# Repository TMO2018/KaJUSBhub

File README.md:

# KaJUSBhub
USB-Adapter zum Einbau in ein C64-Gehäuse für die C64-Tastatur und -Joysticks zum Anschluss an den MiSTer

Auf der Platine enthalten sind:

- ein USB-Adapter dür die C64-Tastatur und -9-pol. Joystcks
- der USB-Hub des MiSTers
- eine über Feinsicherungen abgesicherte Stromversorgung für den MiSter, USB-Adapter und USB-Hub

Die Spannungsversorgung erfolgt mit einem C64-Netzteil.

Rev 0.1:
Version mit einem gemeinsamen Mikrocontroller PIC18F4550 für C64-Tastatur und -Joysticks

Rev 0.2:
Version mit seperaten Mikrocontrollern PIC18F4550 für C64-Tastatur und -Joysticks

Die Firmware basiert auf dem Projekt C64 VICE front-end von Simon Inns.
https://www.waitingforfriday.com/?p=470

Rev 0.1

Hinweis: In den Schaltplänen der Versionen 0.1 und 0.2 ist der Mikrokontroller mit PIC18F4450 beschriftet. Richtig ist aber PIC18F4550. Beide Mikrokontroller sind pin-kompatibel.

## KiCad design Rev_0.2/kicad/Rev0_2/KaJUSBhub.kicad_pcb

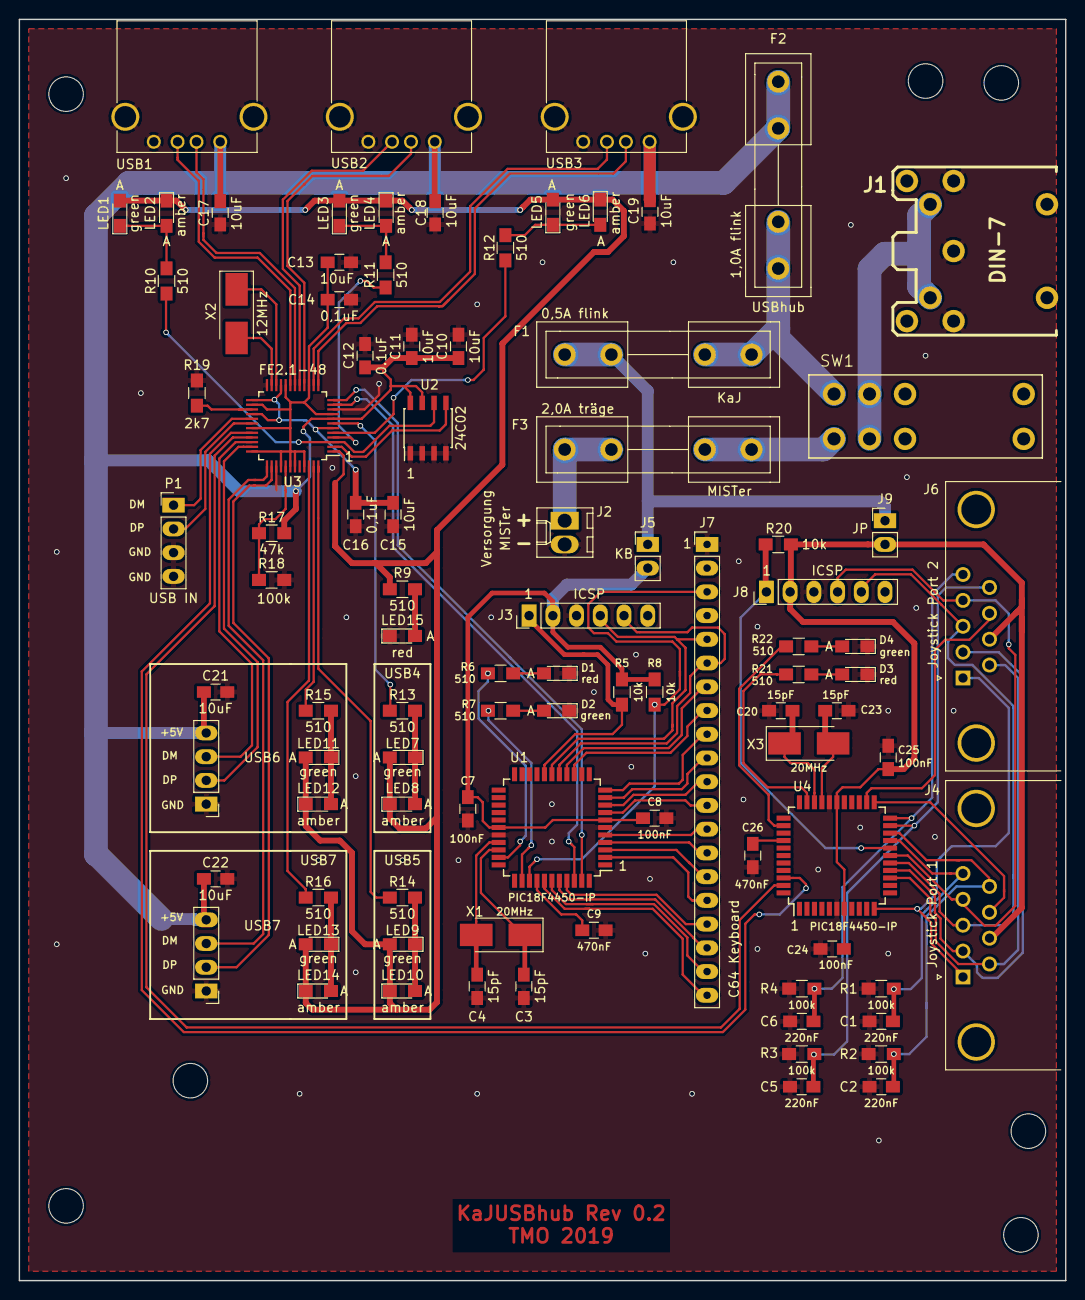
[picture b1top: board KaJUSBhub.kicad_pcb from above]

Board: 2 copper layers, 112.0 x 135.0 mm, 98 parts (0 on the bottom side), 92 nets.

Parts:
C1, C2, C5, C6: 220nF; C_0805_HandSoldering
C3, C4, C20, C23: 15pF; C_0805_HandSoldering
C7, C8, C24, C25: 100nF; C_0805_HandSoldering
C9, C26: 470nF; C_0805_HandSoldering
C10, C11, C13, C15, C17, C18, C19, C21, C22: 10uF; C_0805_HandSoldering
C12: 0.1uF; C_0805_HandSoldering
C14, C16: 0,1uF; C_0805_HandSoldering
D1, D3: red; LED_0805_HandSoldering
D2, D4: green; LED_0805_HandSoldering
F1: 0,5A flink; Fuseholder5x20_horiz_open_inline_Type-I
F2: 1,0A flink; Fuseholder5x20_horiz_open_inline_Type-I
F3: 2,0A träge; Fuseholder5x20_horiz_open_inline_Type-I
J1: DIN-7; din-7
J2: Versorgung MISTer; Molex_KK-6410-02_02x2.54mm_Straight
J3, J8: ICSP; Pin_Header_Straight_1x06_Pitch2.54mm
J4: Joystick Port 1; DSUB-9_Male_Horizontal_Pitch2.77x2.84mm_EdgePinOffset7.70mm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
J5: KB; Pin_Header_Straight_1x02_Pitch2.54mm
J6: Joystick Port 2; DSUB-9_Male_Horizontal_Pitch2.77x2.84mm_EdgePinOffset7.70mm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
J7: C64 Keyboard; Pin_Header_Straight_1x20_Pitch2.54mm_long_pad
J9: JP; Pin_Header_Straight_1x02_Pitch2.54mm
LED1, LED3, LED5, LED7, LED9, LED11, LED13: green; LED_0805_HandSoldering
LED2, LED4, LED6, LED8, LED10, LED12, LED14: amber; LED_0805_HandSoldering
LED15: red; LED_0805_HandSoldering
MH1, MH2, MH3, MH4, MH5: Conn_01x01; MountingHole_3.7mm
P1: USB IN; Pin_Header_Straight_1x04_Pitch2.54mm_long_pad
R1, R2, R3, R4, R18: 100k; R_0805_HandSoldering
R5, R8, R20: 10k; R_0805_HandSoldering
R6, R7, R9, R10, R11, R12, R13, R14, R15, R16, R21, R22: 510; R_0805_HandSoldering
R17: 47k; R_0805_HandSoldering
R19: 2k7; R_0805_HandSoldering
SW1: DPDT_SWITCH
U1, U4: PIC18F4450-IP; TQFP-44_10x10mm_Pitch0.8mm
U2: 24C02; SOIC-8_3.9x4.9mm_Pitch1.27mm
U3: FE2.1-48; LQFP-48_7x7mm_Pitch0.5mm
USB1, USB2, USB3: USB_A
USB6: USB out; Pin_Header_Straight_1x04_Pitch2.54mm_long_pad
USB7: USB out; Pin_Header_Straight_1x04_Pitch2.54mm
X1, X3: 20MHz; Crystal_SMD_5032-2pin_5.0x3.2mm_HandSoldering
X2: 12MHz; Crystal_SMD_5032-2pin_5.0x3.2mm_HandSoldering

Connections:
+5VJP: C24.2, C25.1, J4.7, J6.7, J8.2, J9.2, R20.1, U4.7, U4.28
+5VKB: C7.2, C8.2, J3.2, J5.2, R5.1, R8.1, U1.7, U1.28
+5VKaJ: F1.1, J5.1, J9.1
+5VUSBhub: C10.1, C11.1, C12.1, C17.1, C18.1, C19.1, C21.1, C22.1, F2.1, R17.2, U2.7, U2.8, U3.8, USB1.1, USB2.1, USB3.1, USB6.4, USB7.4
DM1: U3.18, USB1.2
DM2: U3.16, USB2.2
DM3: U3.13, USB3.2
DM4: U1.42, U3.11
DM5: U3.32, U4.42
DM6: U3.34, USB6.3
DM7: U3.37, USB7.3
DMU: P1.1, U3.29
DP1: U3.19, USB1.3
DP2: U3.17, USB2.3
DP3: U3.14, USB3.3
DP4: U1.43, U3.12
DP5: U3.33, U4.43
DP6: U3.35, USB6.2
DP7: U3.38, USB7.2
DPU: P1.2, U3.30
DRV: LED1.2, LED2.1, LED3.2, LED4.1, LED5.2, LED6.1, LED7.2, LED8.1, LED9.2, LED10.1, LED11.2, LED12.1, LED13.2, LED14.1, R9.2, U3.1
GND: C1.2, C2.2, C3.2, C4.2, C5.2, C6.2, C7.1, C8.1, C9.1, C10.2, C11.2, C12.2, C13.1, C14.1, C15.1, C16.1, C17.2, C18.2, C19.2, C20.2, C21.2, C22.2, C23.2, C24.1, C25.2, C26.2, D1.1, D2.1, D3.1, D4.1, J1.1, J1.2, J1.3, J2.2, J3.3, J7.1, J8.3, LED15.1, P1.3, P1.4, R1.1, R2.1, R3.1, R4.1, R18.1, R19.2, U1.6, U1.29, U2.1, U2.2, U2.3, U2.4, U3.10, U3.24, U3.39, U4.6, U4.29, USB1.4, USB1.5, USB2.4, USB2.5, USB3.4, USB3.5, USB6.1, USB7.1
ISCP_JP: J8.1, R20.2, U4.18
J6:1-U1:1: J3.1, R5.2, U1.18
Joy1select: J4.8, U4.23
Joy2select: J6.8, U4.24
LED1: R10.1, U2.6, U3.3
LED2: R11.1, U3.4
LED3: R12.1, U3.5
LED4: R13.1, U3.7
LED5: R14.1, U3.48
LED6: R15.1, U3.47
LED7: R16.1, U3.46
unnamed: C3.1, U1.31, X1.1
unnamed: C4.1, U1.30, X1.2
unnamed: C9.2, U1.37
unnamed: C20.1, U4.31, X3.1
unnamed: C23.1, U4.30, X3.2
unnamed: C26.1, U4.37
unnamed: D1.2, R6.1
unnamed: D2.2, R7.1
unnamed: D3.2, R21.1
unnamed: D4.2, R22.1
unnamed: F1.2, F2.2, SW1.1
unnamed: F3.1, J2.1
unnamed: F3.2, SW1.4
unnamed: J1.4, J1.5, SW1.2, SW1.5
unnamed: LED1.1, LED2.2, R10.2
unnamed: LED3.1, LED4.2, R11.2
unnamed: LED5.1, LED6.2, R12.2
unnamed: LED7.1, LED8.2, R13.2
unnamed: LED9.1, LED10.2, R14.2
unnamed: LED11.1, LED12.2, R15.2
unnamed: LED13.1, LED14.2, R16.2
unnamed: LED15.2, R9.1
unnamed: R6.2, U1.32
unnamed: R7.2, U1.35
unnamed: R17.1, R18.2, U3.41
unnamed: R19.1, U3.27
unnamed: R21.2, U4.32
unnamed: R22.2, U4.35
unnamed: U2.5, U3.2
unnamed: U3.22, X2.1
unnamed: U3.23, X2.2
PX1: C2.1, J4.9, R2.2, U4.20
PX2: C5.1, J6.9, R3.2, U4.21
PY1: C1.1, J4.5, R1.2, U4.19
PY2: C6.1, J6.5, R4.2, U4.22
VD18: C15.2, C16.2, U3.6, U3.21, U3.25, U3.28
VDD33: C13.2, C14.2, U3.9, U3.15, U3.20, U3.26, U3.31, U3.36, U3.40, U3.42, U3.43, U3.45
k0: J7.12, U1.8
k1: J7.11, U1.9
k2: J7.10, U1.10
k3: J7.9, U1.11
k3J: J4.1, J6.1, U4.11
k4: J7.8, U1.14
k4J: J4.6, J6.6, U4.14
k5: J7.7, U1.15
k5J: J4.2, J6.2, U4.15
k6: J3.5, J7.6, U1.16
k6J: J4.3, J6.3, J8.5, U4.16
k7: J3.4, J7.5, U1.17
k7J: J4.4, J6.4, J8.4, U4.17
k8: J7.3, R8.2, U1.36
kA: J7.20, U1.38
kB: J7.19, U1.39
kC: J7.18, U1.40
kD: J7.17, U1.41
kE: J7.16, U1.2
kF: J7.15, U1.3
kG: J7.14, U1.4
kH: J7.13, U1.5
